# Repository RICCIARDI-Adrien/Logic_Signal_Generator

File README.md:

# Logic Signal Generator

A versatile multi-protocol 1.8V/3.3V/5V logic signal generator powered by a PIC18F25K50.

## Features

* 8 independant channels featuring several standard protocols.
* The microcontroller hardware I2C, UART, SPI and PWM modules are used to provide the signal timings.
* Entirely USB-powered, no need for an external power supply.
* Dedicated power supplies and ground connector to easily power the device under test. The embedded 1.8V and 3.3V power supplies are each able to provide 500mA (these power supplies are derived from the USB power, so the available power could be limited by the USB port).
* On-board switch to quickly select the logic signals output voltage (1.8V, 3.3V or 5V).
* The USB interface is managed by the microcontroller itself and provides a standard USB serial port to the host.
* Simple shell-based text interface through the serial port to interactively configure and define the logic signals to generate.
* The signals are doubled on the output connector to easily connect a logic analyzer.
* PICkit-compatible standard connector to easily program the on-board microcontroller firmware.
* Compact and robust casing designed to bring the signal generator on field.

## Hardware

Bare PCB :

Assembled PCB :

## Casing

The casing is made of 4mm-thick 304 stainless steel.

Bare plates :

Assembled bottom plate, with PCB and hex spacers :

Fully assembled device :  
Top view :

IO and power connectors :

USB connector and IO voltage selection switch :

Power and activity LEDs along with microcontroller programming connector :

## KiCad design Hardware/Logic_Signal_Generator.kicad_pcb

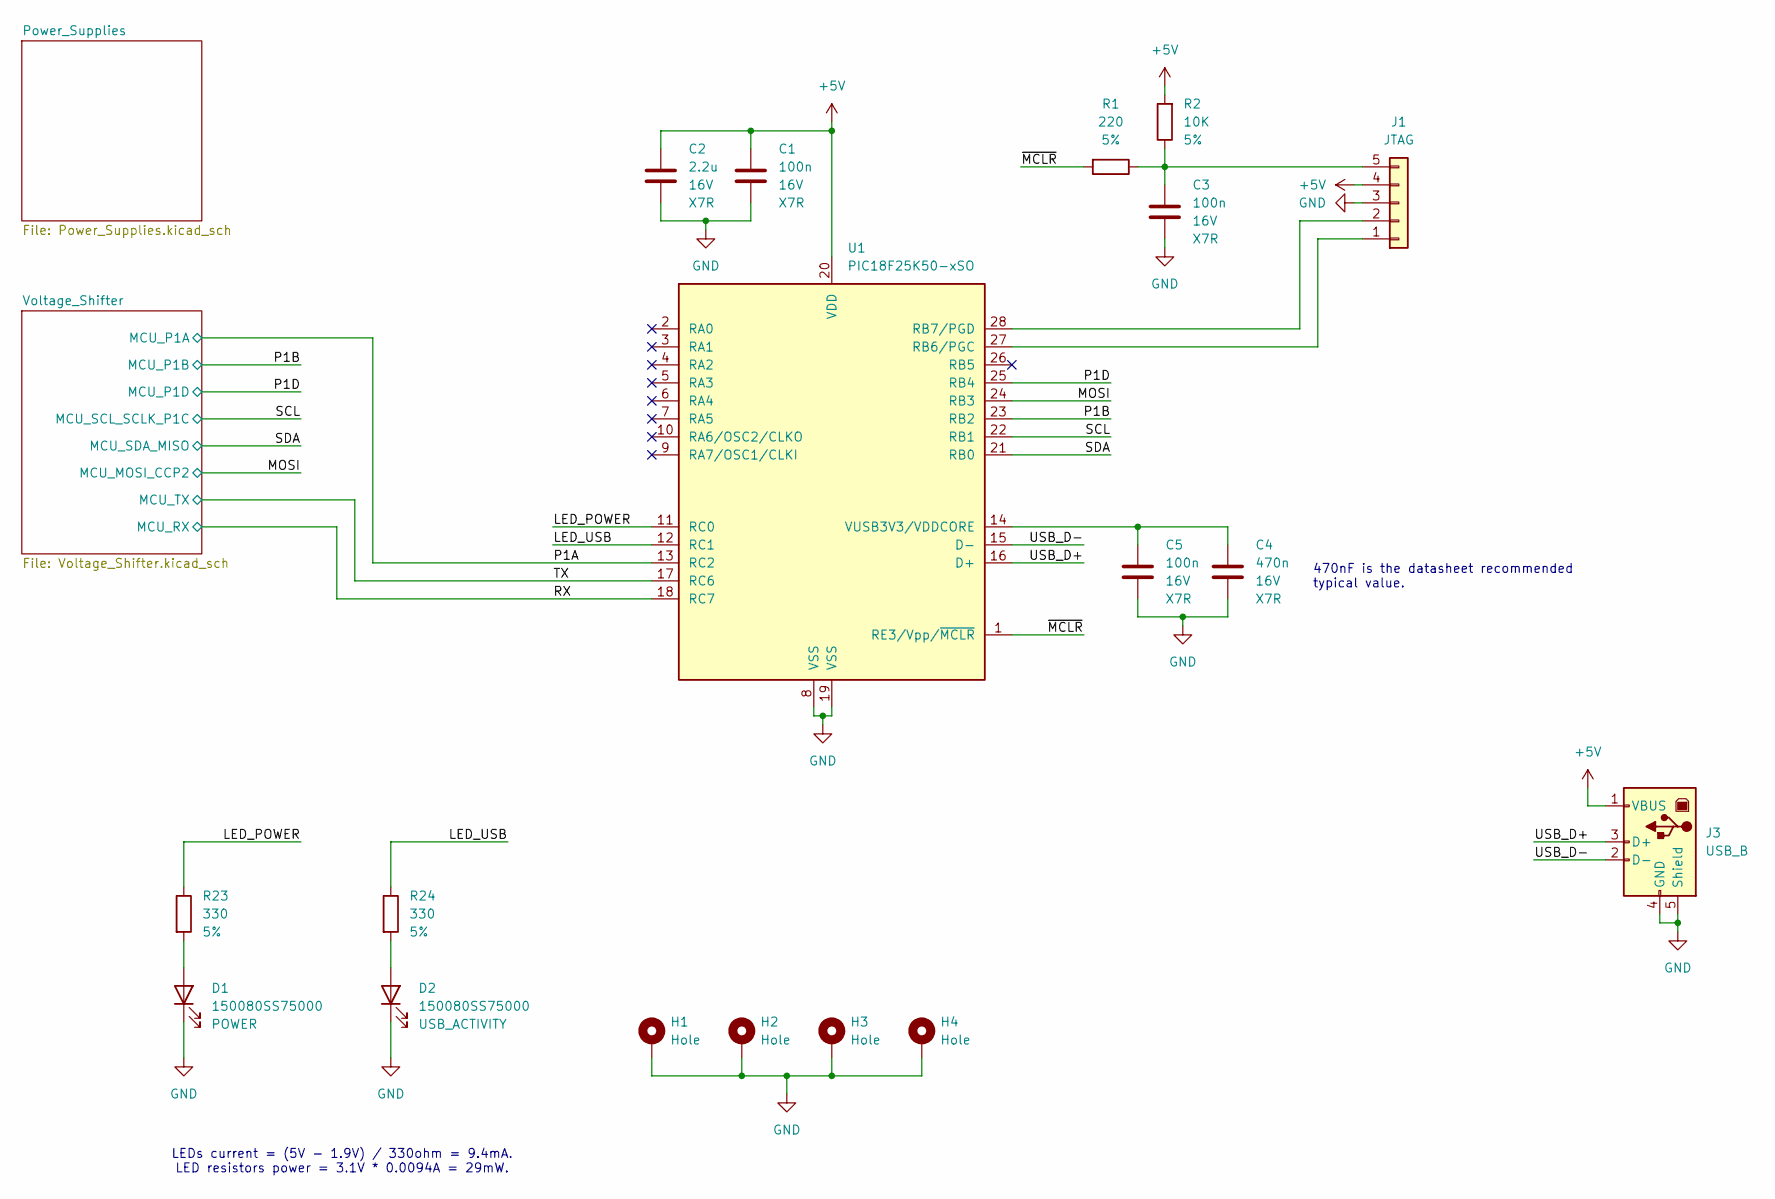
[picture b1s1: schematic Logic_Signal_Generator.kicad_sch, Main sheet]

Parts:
C1, C3, C5: 100n; C_0603_1608Metric_Pad1.08x0.95mm_HandSolder
C2: 2.2u; C_0805_2012Metric_Pad1.18x1.45mm_HandSolder
C4: 470n; C_0603_1608Metric_Pad1.08x0.95mm_HandSolder
D1, D2: 150080SS75000; LED_0805_2012Metric_Pad1.15x1.40mm_HandSolder
H1, H2, H3, H4: Hole; MountingHole_4.5mm_Pad_Via
J1: JTAG; PinHeader_1x05_P2.54mm_Horizontal
J3: USB_B; USB_B_Lumberg_2411_02_Horizontal
R1: 220; R_0603_1608Metric_Pad0.98x0.95mm_HandSolder
R2: 10K; R_0603_1608Metric_Pad0.98x0.95mm_HandSolder
R23, R24: 330; R_1206_3216Metric_Pad1.30x1.75mm_HandSolder
U1: PIC18F25K50-xSO; SOIC-28W_7.5x17.9mm_P1.27mm

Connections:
+5V: C1.1, C2.1, J1.4, J3.1 (VBUS), R2.2, U1.20 (VDD); also elsewhere on the board
/LED_POWER: R23.1, U1.11 (RC0)
/LED_USB: R24.1, U1.12 (RC1)
/MOSI: U1.24 (RB3); also elsewhere on the board
/P1A: U1.13 (RC2); also elsewhere on the board
/P1B: U1.23 (RB2); also elsewhere on the board
/P1D: U1.25 (RB4); also elsewhere on the board
/RX: U1.18 (RC7); also elsewhere on the board
/SCL: U1.22 (RB1); also elsewhere on the board
/SDA: U1.21 (RB0); also elsewhere on the board
/TX: U1.17 (RC6); also elsewhere on the board
/USB_D+: J3.3 (D+), U1.16 (D+)
/USB_D-: J3.2 (D-), U1.15 (D-)
/~MCLR: R1.2, U1.1 (RE3/Vpp/~MCLR)
GND: C1.2, C2.2, C3.2, C4.2, C5.2, D1.1 (K), D2.1 (K), H1.1, H2.1, H3.1, H4.1, J1.3, J3.4 (GND), J3.5 (Shield), U1.8 (VSS), U1.19 (VSS); also elsewhere on the board
unnamed: D1.2 (A), R23.2
unnamed: D2.2 (A), R24.2
unnamed: J1.1, U1.27 (RB6/PGC)
unnamed: J1.2, U1.28 (RB7/PGD)
unnamed: C3.1, J1.5, R1.1, R2.1
unnamed: C4.1, C5.1, U1.14 (VUSB3V3/VDDCORE)

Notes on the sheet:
LEDs current = (5V - 1.9V) / 330ohm = 9.4mA. LED resistors power = 3.1V * 0.0094A = 29mW.
470nF is the datasheet recommended typical value.

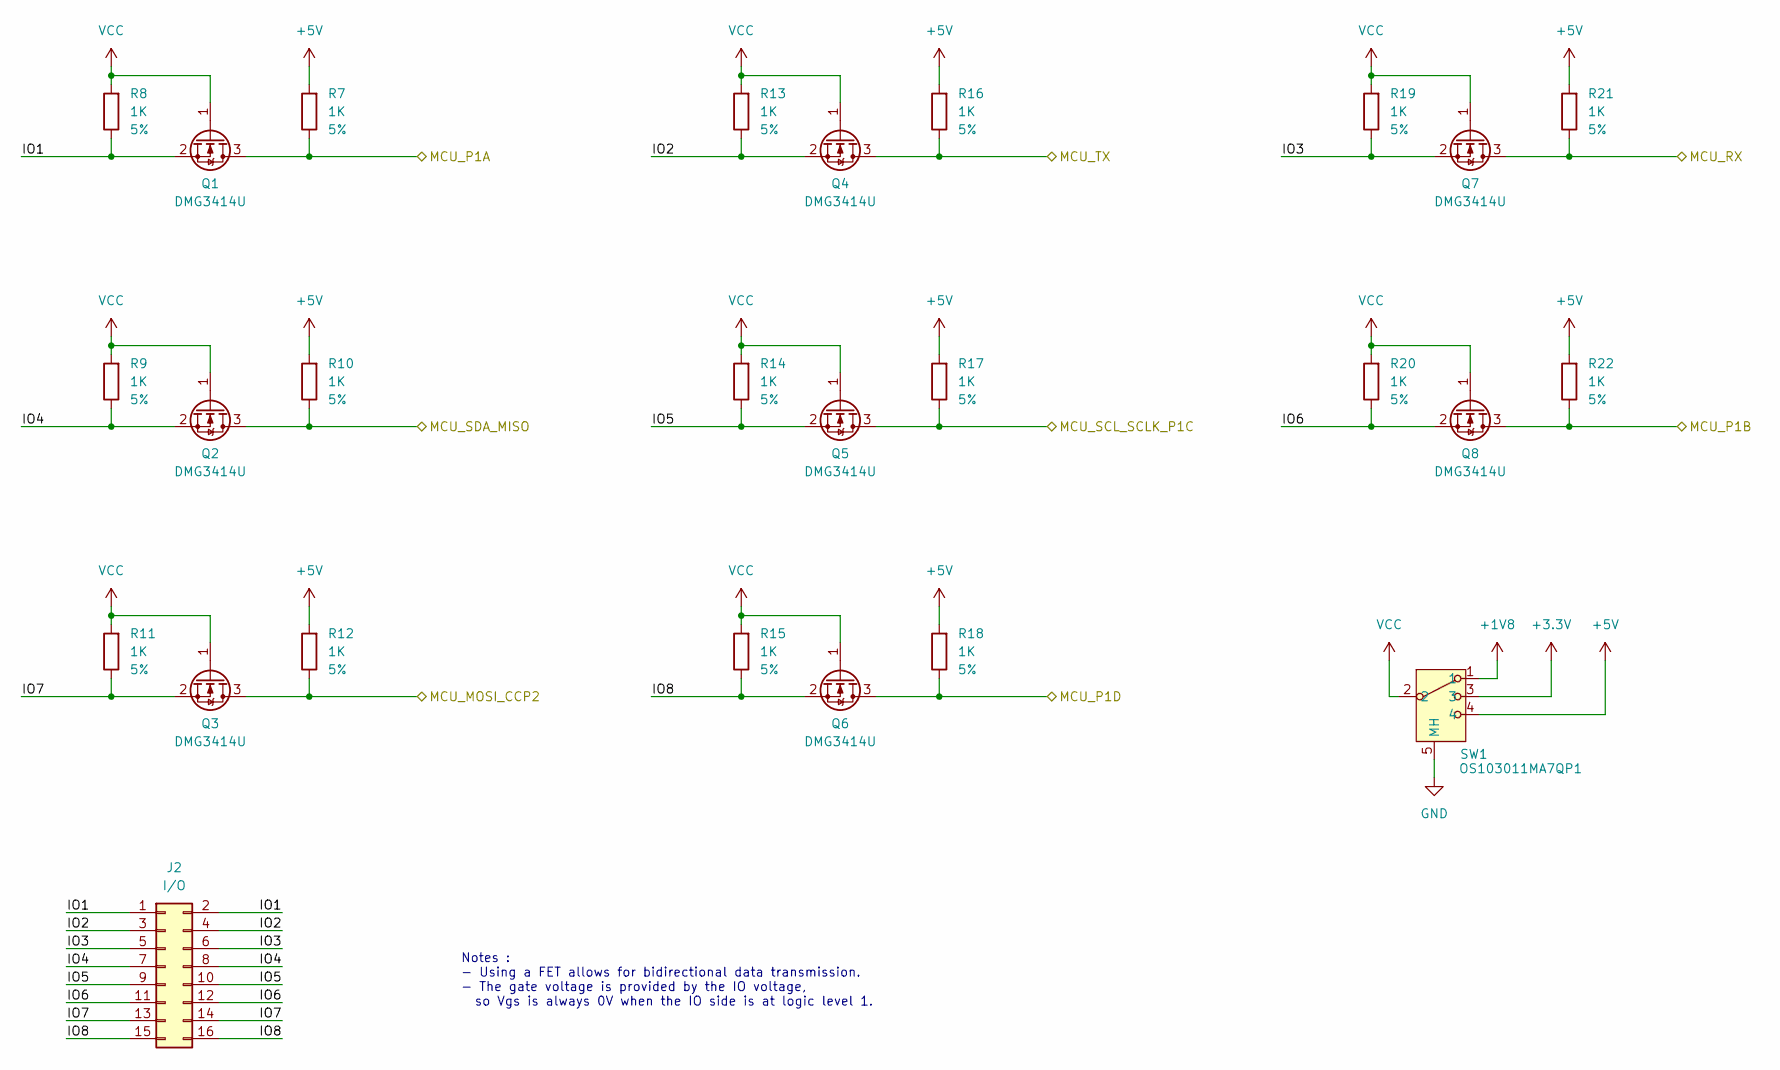
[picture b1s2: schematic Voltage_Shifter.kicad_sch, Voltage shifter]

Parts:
J2: I/O; PinHeader_2x08_P2.54mm_Horizontal
Q1, Q2, Q3, Q4, Q5, Q6, Q7, Q8: DMG3414U; SOT-23
R7, R8, R9, R10, R11, R12, R13, R14, R15, R16, R17, R18, R19, R20, R21, R22: 1K; R_0603_1608Metric_Pad0.98x0.95mm_HandSolder
SW1: OS103011MA7QP1

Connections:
+1V8: SW1.1; also elsewhere on the board
+3.3V: SW1.3; also elsewhere on the board
+5V: R7.2, R10.2, R12.2, R16.2, R17.2, R18.2, R21.2, R22.2, SW1.4; also elsewhere on the board
/MOSI: Q3.3 (D), R12.1; also elsewhere on the board
/P1A: Q1.3 (D), R7.1; also elsewhere on the board
/P1B: Q8.3 (D), R22.1; also elsewhere on the board
/P1D: Q6.3 (D), R18.1; also elsewhere on the board
/RX: Q7.3 (D), R21.1; also elsewhere on the board
/SCL: Q5.3 (D), R17.1; also elsewhere on the board
/SDA: Q2.3 (D), R10.1; also elsewhere on the board
/TX: Q4.3 (D), R16.1; also elsewhere on the board
/Voltage_Shifter/IO1: J2.1, J2.2, Q1.2 (S), R8.1
/Voltage_Shifter/IO2: J2.3, J2.4, Q4.2 (S), R13.1
/Voltage_Shifter/IO3: J2.5, J2.6, Q7.2 (S), R19.1
/Voltage_Shifter/IO4: J2.7, J2.8, Q2.2 (S), R9.1
/Voltage_Shifter/IO5: J2.9, J2.10, Q5.2 (S), R14.1
/Voltage_Shifter/IO6: J2.11, J2.12, Q8.2 (S), R20.1
/Voltage_Shifter/IO7: J2.13, J2.14, Q3.2 (S), R11.1
/Voltage_Shifter/IO8: J2.15, J2.16, Q6.2 (S), R15.1
GND: SW1.5 (MH), SW1.6 (MH); also elsewhere on the board
VCC: Q1.1 (G), Q2.1 (G), Q3.1 (G), Q4.1 (G), Q5.1 (G), Q6.1 (G), Q7.1 (G), Q8.1 (G), R8.2, R9.2, R11.2, R13.2, R14.2, R15.2, R19.2, R20.2, SW1.2

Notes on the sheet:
Notes : - Using a FET allows for bidirectional data transmission. - The gate voltage is provided by the IO voltage, so Vgs is always 0V when the IO side is at logic level 1.

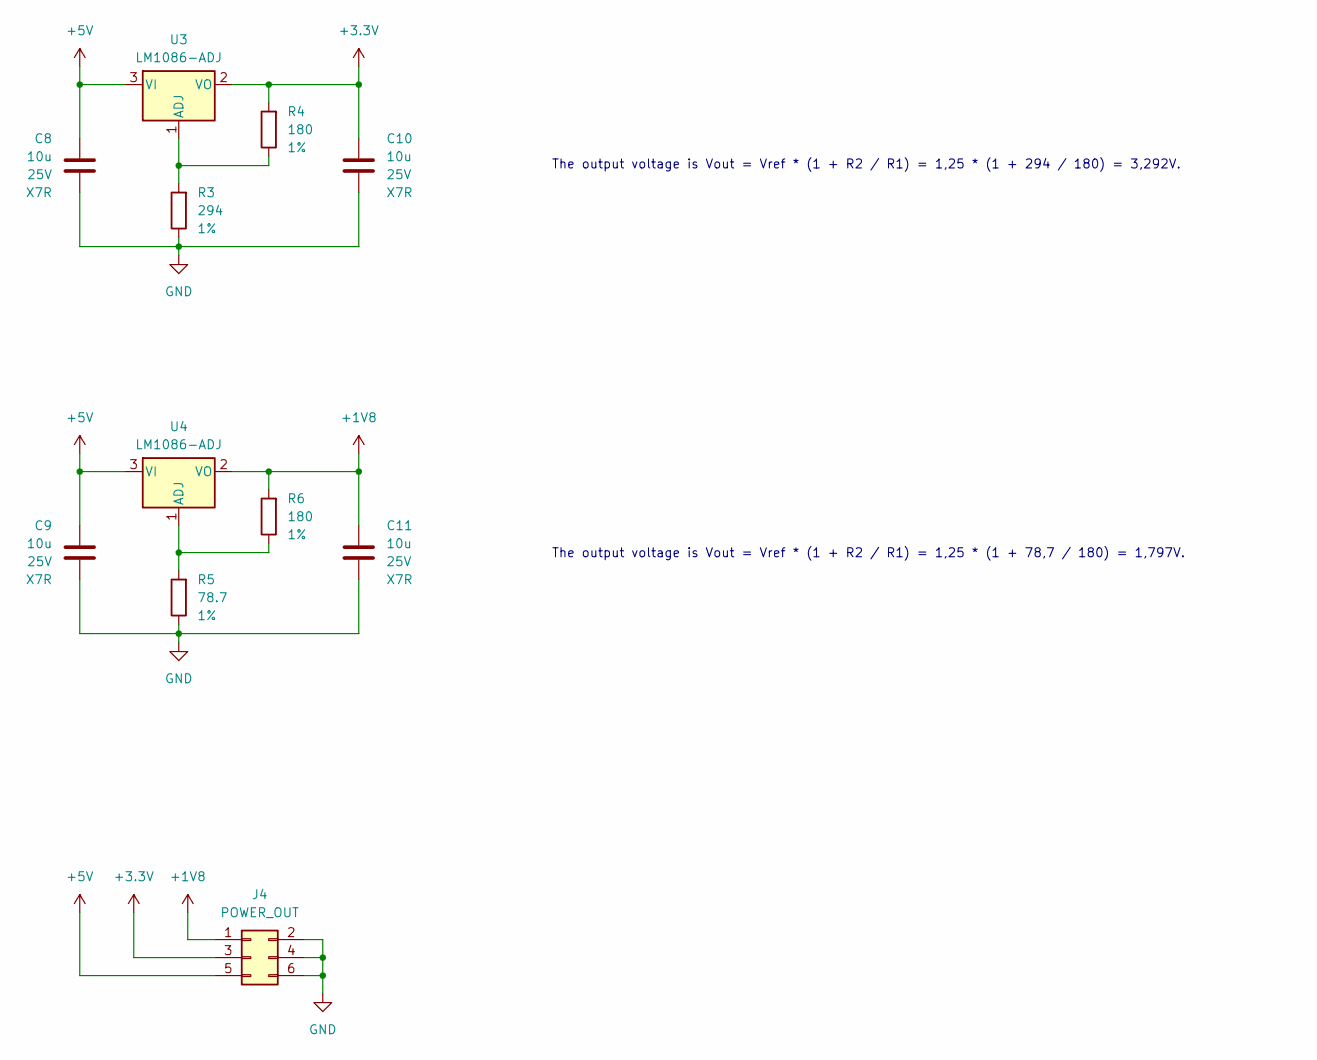
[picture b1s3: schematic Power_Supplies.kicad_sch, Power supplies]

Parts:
C8, C9, C10, C11: 10u; C_0805_2012Metric_Pad1.18x1.45mm_HandSolder
J4: POWER_OUT; PinHeader_2x03_P2.54mm_Horizontal
R3: 294; R_0603_1608Metric_Pad0.98x0.95mm_HandSolder
R4, R6: 180; R_0603_1608Metric_Pad0.98x0.95mm_HandSolder
R5: 78.7; R_0603_1608Metric_Pad0.98x0.95mm_HandSolder
U3, U4: LM1086-ADJ; TO-263-3_TabPin2

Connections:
+1V8: C11.1, J4.1, R6.2, U4.2 (VO); also elsewhere on the board
+3.3V: C10.1, J4.3, R4.2, U3.2 (VO); also elsewhere on the board
+5V: C8.1, C9.1, J4.5, U3.3 (VI), U4.3 (VI); also elsewhere on the board
GND: C8.2, C9.2, C10.2, C11.2, J4.2, J4.4, J4.6, R3.1, R5.1; also elsewhere on the board
unnamed: R3.2, R4.1, U3.1 (ADJ)
unnamed: R5.2, R6.1, U4.1 (ADJ)

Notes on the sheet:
The output voltage is Vout = Vref * (1 + R2 / R1) = 1,25 * (1 + 294 / 180) = 3,292V.
The output voltage is Vout = Vref * (1 + R2 / R1) = 1,25 * (1 + 78,7 / 180) = 1,797V.

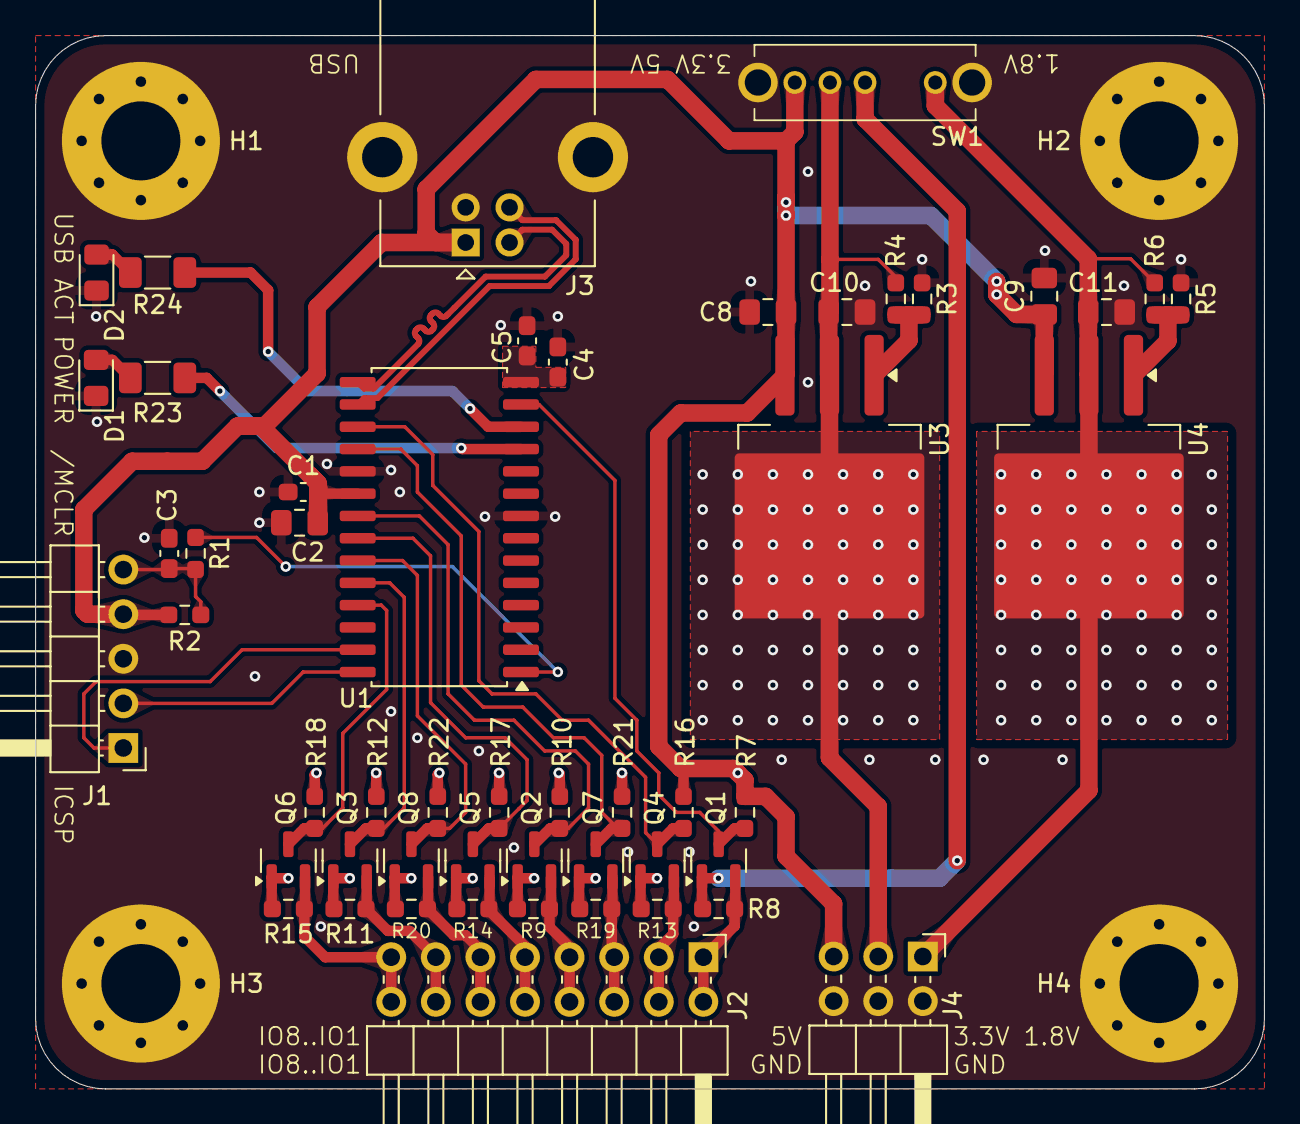
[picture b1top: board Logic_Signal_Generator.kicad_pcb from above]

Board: 2 copper layers, 70.0 x 60.0 mm, 55 parts (0 on the bottom side), 34 nets.

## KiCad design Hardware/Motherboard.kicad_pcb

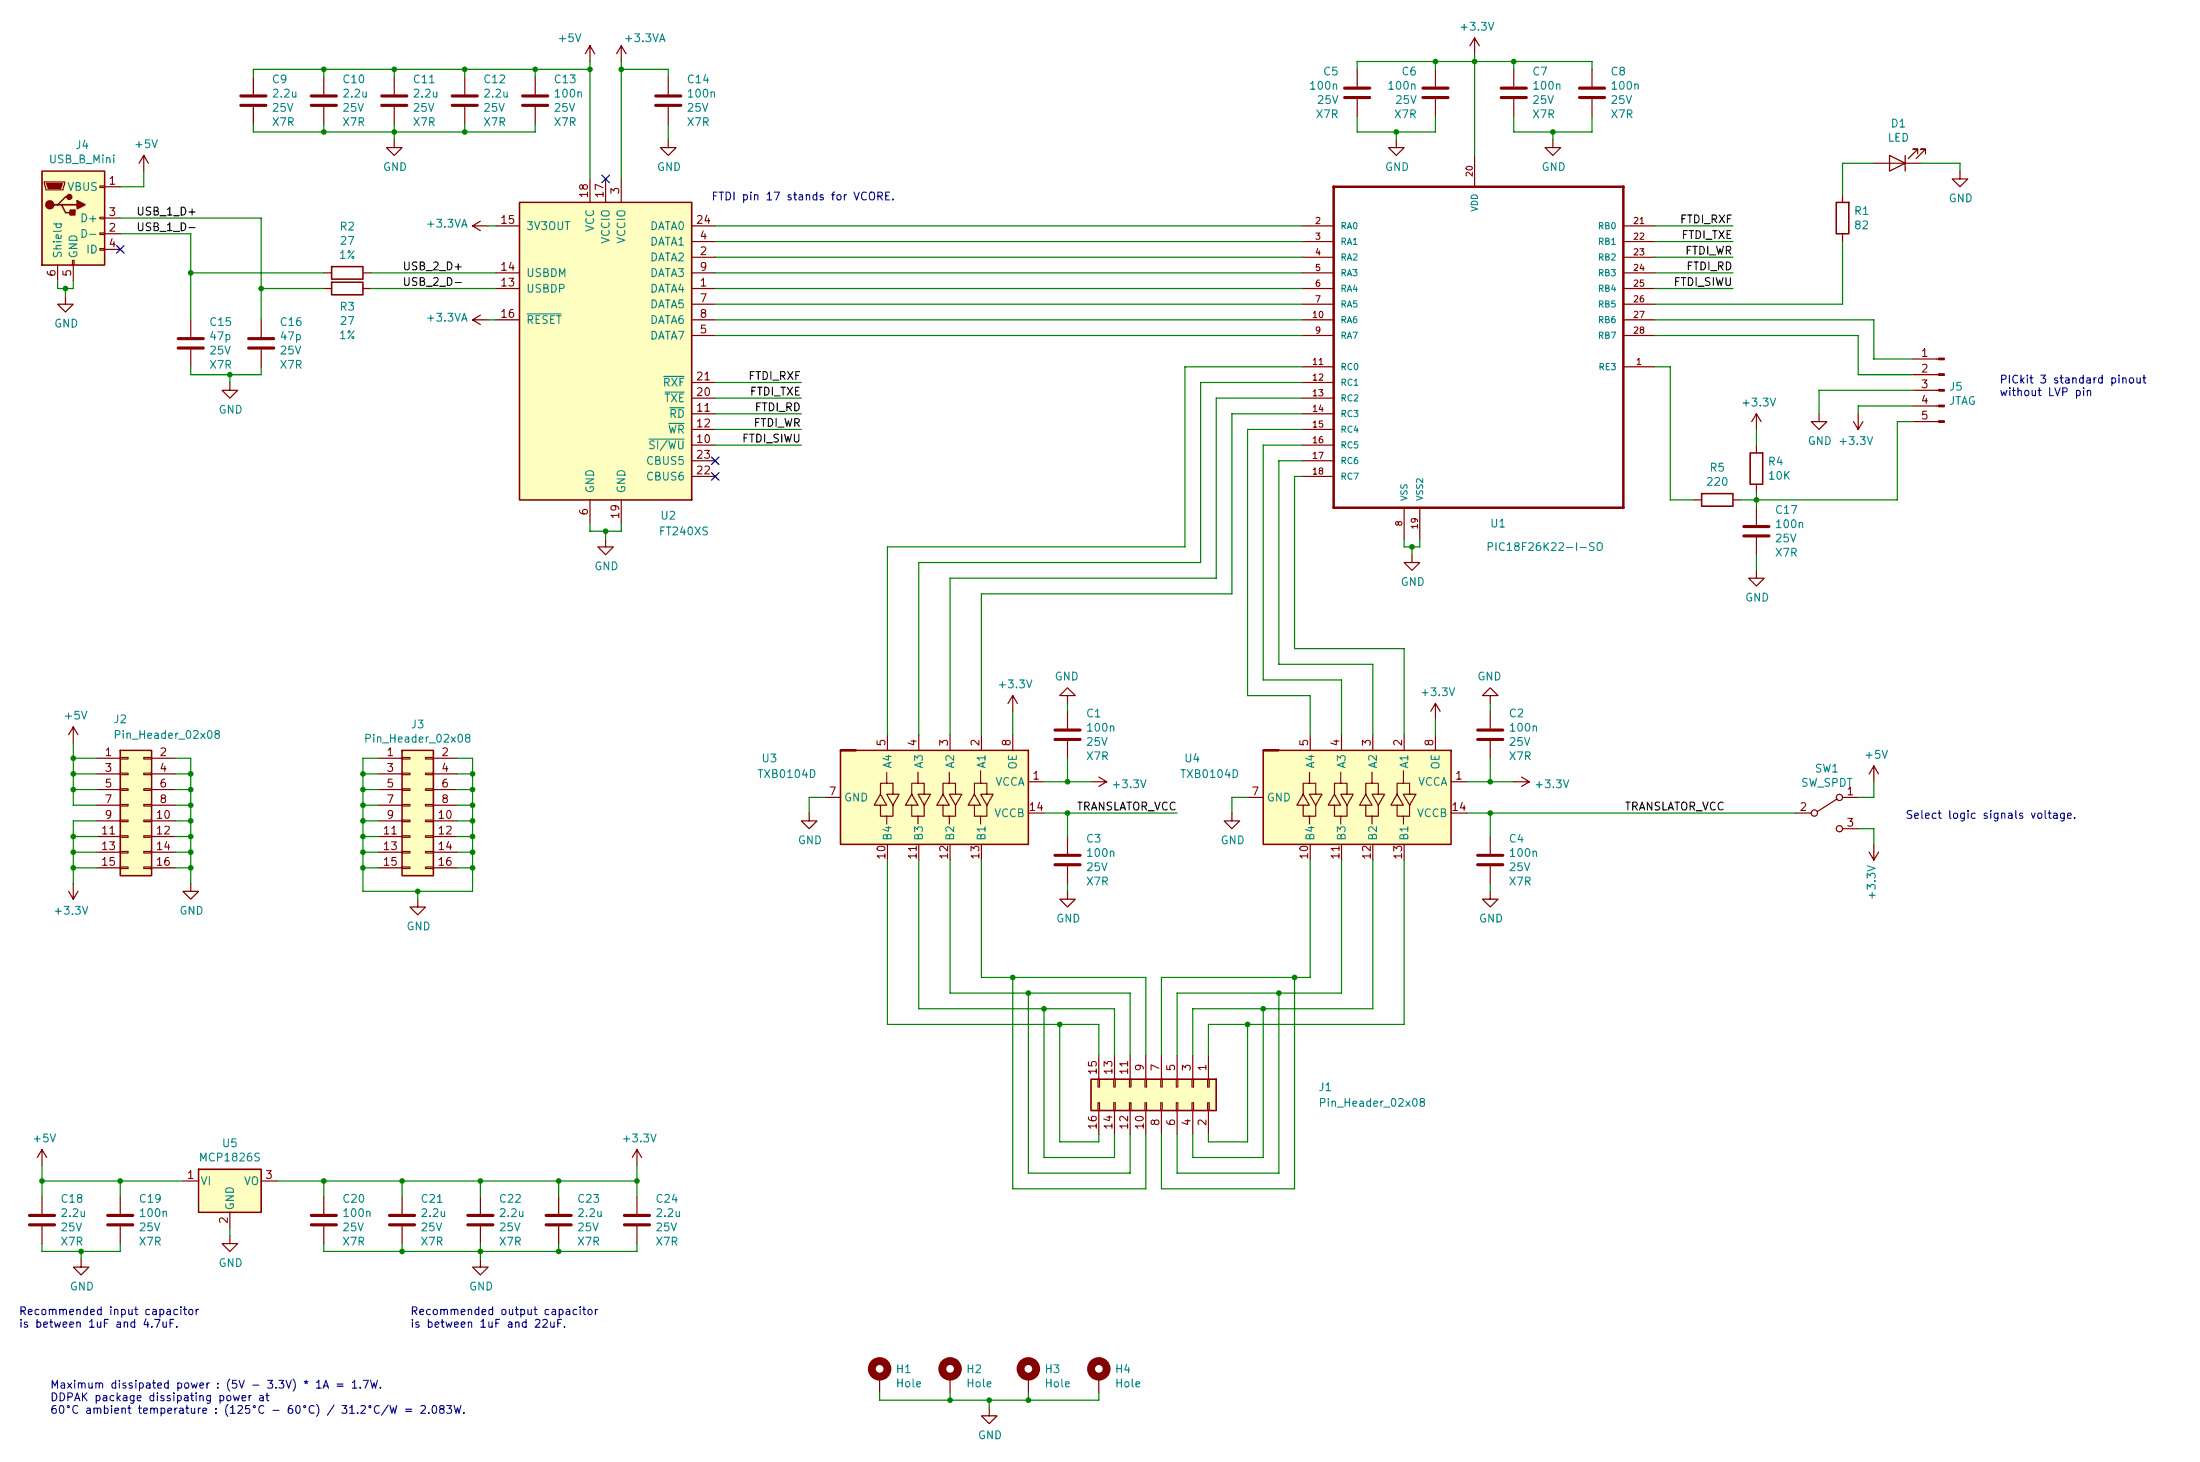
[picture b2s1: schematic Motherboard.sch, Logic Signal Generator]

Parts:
C1, C2, C3, C4, C5, C6, C7, C8, C13, C14, C17, C19, C20: 100n; C_0805_2012Metric_Pad1.15x1.40mm_HandSolder
C9, C10, C11, C12, C18, C21, C22, C23, C24: 2.2u; C_0805_2012Metric_Pad1.15x1.40mm_HandSolder
C15, C16: 47p; C_0805_2012Metric_Pad1.15x1.40mm_HandSolder
D1: LED; LED_D5.0mm
H1, H2, H3, H4: Hole; MountingHole_3mm_Pad
J1, J2, J3: Pin_Header_02x08; PinHeader_2x08_P2.54mm_Horizontal
J4: USB_B_Mini; USB_Mini-B_Lumberg_2486_01_Horizontal
J5: JTAG; PinHeader_1x05_P2.54mm_Horizontal
R1: 82; R_1206_3216Metric_Pad1.42x1.75mm_HandSolder
R2, R3: 27; R_0805_2012Metric_Pad1.15x1.40mm_HandSolder
R4: 10K; R_1206_3216Metric_Pad1.42x1.75mm_HandSolder
R5: 220; R_1206_3216Metric_Pad1.42x1.75mm_HandSolder
SW1: SW_SPDT; SW_CuK_OS102011MA1QN1_SPDT_Angled
U1: PIC18F26K22-I-SO; SOIC-28W_7.5x17.9mm_P1.27mm
U2: FT240XS; SSOP-24_3.9x8.7mm_P0.635mm
U3, U4: TXB0104D; SOIC-14_3.9x8.7mm_P1.27mm
U5: MCP1826S; TO-263-3_TabPin2

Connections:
+3.3VA: C14.1, U2.3 (VCCIO), U2.15 (3V3OUT), U2.16 (~RESET)
+3V3: C1.2, C2.2, C5.1, C6.1, C7.1, C8.1, C20.1, C21.1, C22.1, C23.1, C24.1, J2.9, J2.11, J2.13, J2.15, J5.4, R4.2, SW1.3 (C), U1.20 (VDD), U3.1 (VCCA), U3.8 (OE), U4.1 (VCCA), U4.8 (OE), U5.3 (VO)
+5V: C9.1, C10.1, C11.1, C12.1, C13.1, C18.1, C19.1, J2.1, J2.3, J2.5, J2.7, J4.1 (VBUS), SW1.1 (A), U2.18 (VCC), U5.1 (VI)
/FTDI_RD: U1.24 (RB3), U2.11 (~RD)
/FTDI_RXF: U1.21 (RB0), U2.21 (~RXF)
/FTDI_SIWU: U1.25 (RB4), U2.10 (~SI/WU)
/FTDI_TXE: U1.22 (RB1), U2.20 (~TXE)
/FTDI_WR: U1.23 (RB2), U2.12 (~WR)
/TRANSLATOR_VCC: C3.1, C4.1, SW1.2 (B), U3.14 (VCCB), U4.14 (VCCB)
/USB_1_D+: C16.1, J4.3 (D+), R3.2
/USB_1_D-: C15.1, J4.2 (D-), R2.2
/USB_2_D+: R2.1, U2.14 (USBDM)
/USB_2_D-: R3.1, U2.13 (USBDP)
GND: C1.1, C2.1, C3.2, C4.2, C5.2, C6.2, C7.2, C8.2, C9.2, C10.2, C11.2, C12.2, C13.2, C14.2, C15.2, C16.2, C17.2, C18.2, C19.2, C20.2, C21.2, C22.2, C23.2, C24.2, D1.1 (K), H1.1, H2.1, H3.1, H4.1, J2.2, J2.4, J2.6, J2.8, J2.10, J2.12, J2.14, J2.16, J3.1, J3.2, J3.3, J3.4, J3.5, J3.6, J3.7, J3.8, J3.9, J3.10, J3.11, J3.12, J3.13, J3.14, J3.15, J3.16, J4.5 (GND), J4.6 (Shield), J5.3, U1.8 (VSS), U1.19 (VSS2), U2.6 (GND), U2.19 (GND), U3.7 (GND), U4.7 (GND), U5.2 (GND)
unnamed: C17.1, J5.5, R4.1, R5.1
unnamed: D1.2 (A), R1.2
unnamed: J1.1, J1.2, U4.13 (B1)
unnamed: J1.3, J1.4, U4.12 (B2)
unnamed: J1.5, J1.6, U4.11 (B3)
unnamed: J1.7, J1.8, U4.10 (B4)
unnamed: J1.9, J1.10, U3.13 (B1)
unnamed: J1.11, J1.12, U3.12 (B2)
unnamed: J1.13, J1.14, U3.11 (B3)
unnamed: J1.15, J1.16, U3.10 (B4)
unnamed: J5.1, U1.27 (RB6)
unnamed: J5.2, U1.28 (RB7)
unnamed: R1.1, U1.26 (RB5)
unnamed: R5.2, U1.1 (RE3)
unnamed: U1.2 (RA0), U2.24 (DATA0)
unnamed: U1.3 (RA1), U2.4 (DATA1)
unnamed: U1.4 (RA2), U2.2 (DATA2)
unnamed: U1.5 (RA3), U2.9 (DATA3)
unnamed: U1.6 (RA4), U2.1 (DATA4)
unnamed: U1.7 (RA5), U2.7 (DATA5)
unnamed: U1.9 (RA7), U2.5 (DATA7)
unnamed: U1.10 (RA6), U2.8 (DATA6)
unnamed: U1.11 (RC0), U3.5 (A4)
unnamed: U1.12 (RC1), U3.4 (A3)
unnamed: U1.13 (RC2), U3.3 (A2)
unnamed: U1.14 (RC3), U3.2 (A1)
unnamed: U1.15 (RC4), U4.5 (A4)
unnamed: U1.16 (RC5), U4.4 (A3)
unnamed: U1.17 (RC6), U4.3 (A2)
unnamed: U1.18 (RC7), U4.2 (A1)

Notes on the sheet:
PICkit 3 standard pinout without LVP pin
Maximum dissipated power : (5V - 3.3V) * 1A = 1.7W. DDPAK package dissipating power at 60°C ambient temperature : (125°C - 60°C) / 31.2°C/W = 2.083W.
Recommended input capacitor is between 1uF and 4.7uF.
Recommended output capacitor is between 1uF and 22uF.
FTDI pin 17 stands for VCORE.
Select logic signals voltage.

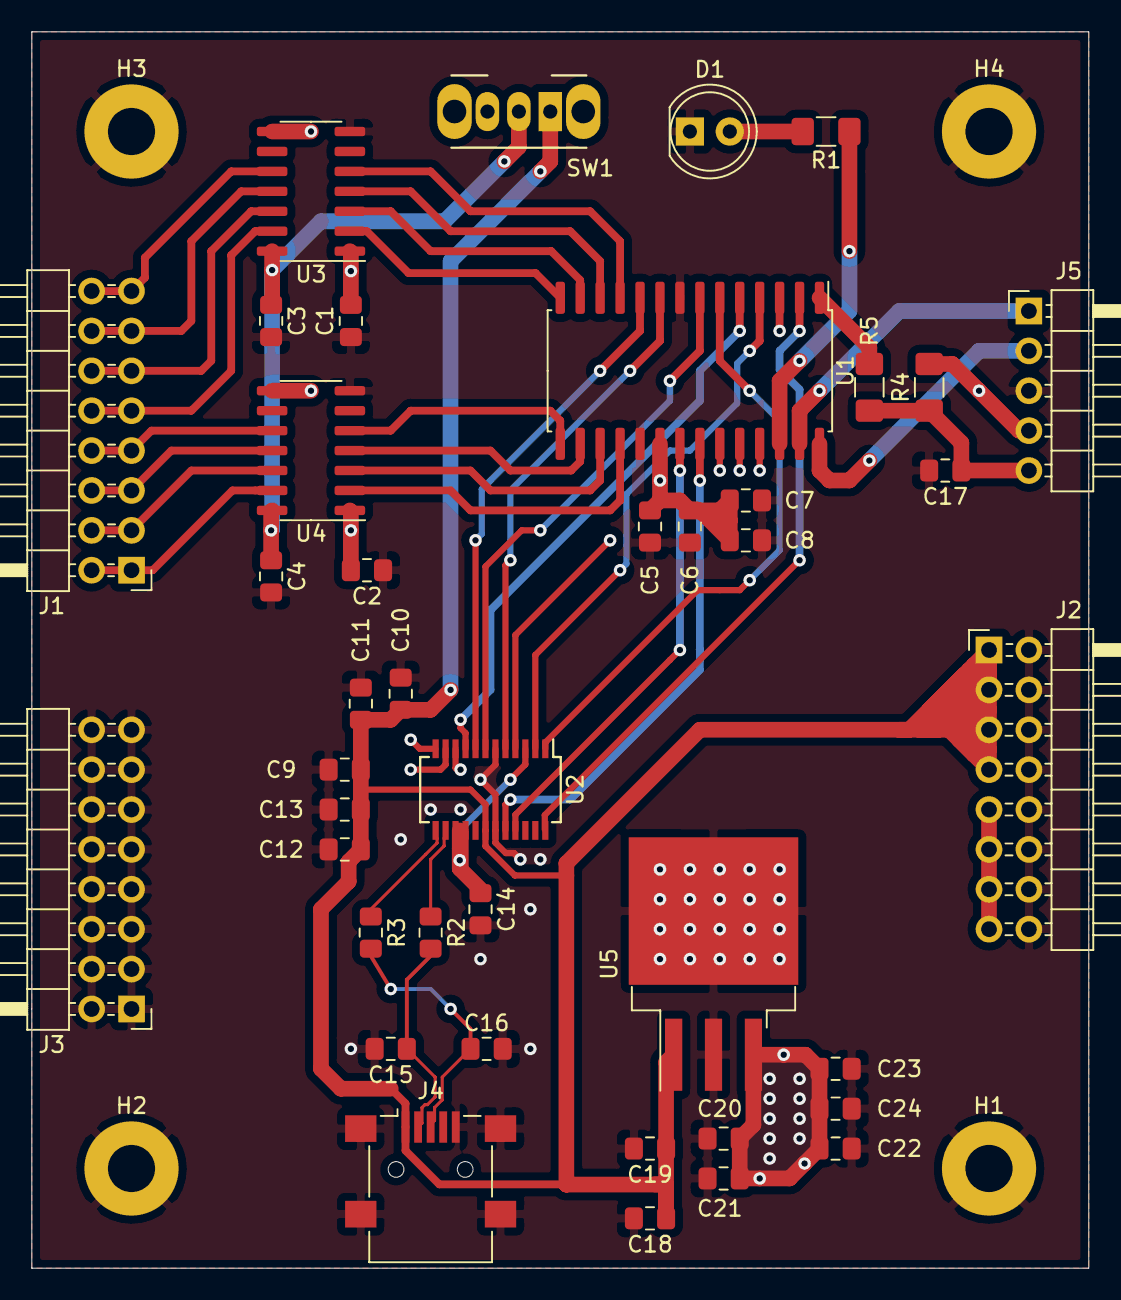
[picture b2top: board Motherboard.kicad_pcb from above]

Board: 4 copper layers, 67.3 x 78.7 mm, 45 parts (0 on the bottom side), 44 nets.

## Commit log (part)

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2020-04-02 Initial commit. Added .gitignore file.
2020-04-02 [Hardware] Started schematic. Microcontroller, voltage translators and pin headers are present.
2020-04-02 [Hardware] Added LDO and led to schematic.
2020-04-02 [Hardware] Added FTDI FIFO and logic signals output voltage switch to schematic.
2020-04-02 [Hardware] Added PCB mounting holes.
2020-04-02 Added README.md.
2020-04-15 [Hardware] Started PCB routing. Switched to 4 layers to have power supply planes.
2020-04-15 [Hardware] Improved some component names placement on PCB.
2025-04-12 [Software] Created the project empty layout.
2025-04-12 [Software] Added the microcontroller fuses configuration.
2025-04-12 [Software] Configured the system clock and added a blinking LED test.
2025-04-17 [Software] Added the logging module that outputs log messages to the UART.
2025-04-22 [Software] Started exploring and implementing the USB support. The only thing the USB device is currently capable of is to attach to the USB bus.
2025-04-22 [Software] Added the dual-priority interrupts support and the generic handler for the USB peripheral.
    Only the USB 'reset' interrupt is detected for now, and only for test purpose.
2025-04-30 [Software] Enabled the microcontroller clock automatic synchronization with the USB host clock.
2025-04-30 [Software] Added USB 'in' packet support (i.e. transmitting data from the device to the host). The USB stack is now able to transmit the device descriptor to the host.
2025-04-30 [Software] Used bit fields to describe the USB hardware endpoint status register, this makes the code easier to understand.
2025-05-20 [Software] Reorganized the USB interrupt to better manage the IN, OUT and SETUP transfers.
2025-05-20 [Software] Added a basic USB data toggling synchronization support and the beginning of the 'set address' USB enumeration step.
2025-05-20 [Software] Fixed the USB string descriptor indexes in the device descriptor : they start at index 1 instead of 0.
2025-05-20 [Software] Added color to the initial log message, so it can be easily spotted.
2025-07-26 [Software] Added more debugging information displayed at the beginning of the USB interrupt handler.
2025-07-26 [Software] Enabled the generation of a map file during the build.
2025-07-26 [Software] Added the support for the USB Device Qualifier descriptor in the enumeration process.
    Also added the ability to stall an endpoint.
2025-07-26 [Software] Improved the USB interface handling during the configuration descriptors enumeration step.
    It is now possible to manage as much interfaces per configuration as there is room in an endpoint buffer.
2025-07-26 [Software] Removed the USB configuration structure and embedded a pointer to the USB configurations directly into the USB device descriptor.
2025-07-26 [Software] Added support to the USB enumeration step for multiple configuration descriptors.
2025-07-27 [Software] Enabled all compiler warnings.
2025-07-27 [Software] Added logging code section macros that allow to automatically discard the section of code when the logs are disabled.
2025-07-27 [Software] Added support for the USB set configuration enumeration step.
2025-07-27 [Software] Updated the USB core module logs with the log sections.
2025-07-27 [Software] Fixed the 'set configuration' USB enumeration step log message that was not displaying the correct configuration value.
2025-07-31 [Software] Limited the device required current to 500mA, otherwise the host may refuse to select the corresponding USB configuration.
2025-07-31 [Software] Unified the USB device descriptor class and protocol codes.
2025-07-31 [Software] Added the USB interfaces description matching the CDC ACM specifications.
2025-07-31 [Software] Added a way to configure the hardware USB endpoints along with the various descriptors.
2025-07-31 [Software] Replaced the calls to memcpy() in the USB module by a custom macro to fix a weird bug where some unrelated variables were overwritten after the memcpy() call.
2025-07-31 [Software] Added the calling of the appropriate callback when USB data is received by an endpoint.
2025-08-01 [Software] Moved all the handling of non standard USB setup requests to the registered callbacks.
2025-08-01 [Software] Started the implementation of the USB CDC ACM, starting with an empty callback for the ACM control endpoint.
2025-08-01 [Software] Added the USB CDC ACM PSTN Set Line Coding request support.
2025-08-03 [Software] Fixed consecutive USB OUT transfers not triggering the transfer interrupt by clearing the USB interrupt flags in the correct order.
2025-08-03 [Software] Deduplicated the USB USTAT register information retrieval.
2025-08-03 [Software] Added support for the USB handshake ACK packets.
2025-08-03 [Software] Added support for regular USB OUT packets.
2025-08-03 [Software] Fixed the configuration of the USB hardware endpoints other than 0.
2025-08-03 [Software] Added a simple USB CDC echo test.
2025-08-23 [Software] Allowed the USB stack to call a callback when an IN transfer has been terminated and acknowledged.
2025-08-24 [Software] Moved the USB CDC private types from the header to the source file, as they don't need to be public and complexify the API.
2025-08-24 [Software] Added an API function to write an USB CDC ACM data string to the host.
    Also added support for the transmission flow control.
2025-08-24 [Software] Allowed to send USB CDC ACM strings of data exceeding the USB packet size.
2025-08-25 [Software] Added the USB CDC ACM callback that retrieves the received data bytes and stores them into an internal circular buffer.
2025-08-25 [Software] Added USB core macros to enable or disable the USB peripheral interrupts.
2025-08-25 [Software] Added an USB CDC ACM API function to read a received character.
2025-08-25 [Software] Replaced the strlen() call by a custom string size computation in the USBCommunicationsWriteCharacter() function.
    This allows to save some bytes and also to make sure the string computation will behave as expected.
2025-08-25 [Software] Started implementing the shell commands reading.
2025-08-25 [Software] Added a way to detect that the USB CDC ACM communication link is ready.
2025-08-25 [Software] Improved the shell by neutralizing the VT100 escape sequences and adding support for the UNIX Ctrl+C, Ctrl+D and Ctrl+U key combinations.
2025-08-26 [Software] Added the shell commands processing core.
2025-08-26 [Software] Added the shell "help" command.
2025-08-26 [Software] Added a function to more easily compare a shell token with a string.
2025-08-26 [Software] Added the "i2C-configure" shell command.
2025-08-26 [Software] Added the API function to configure the MSSP peripheral as I2C master.
    Also renamed the MSSPI2CSetFrequency() function to automatically gather all I2C and future SPI functions.
2025-08-26 [Software] Added the I2C start, stop, read and write API functions.
2025-08-30 [Software] Added an utility function to convert a hexadecimal number from a string to its binary representation.
2025-08-30 [Software] Started implementing the "i2c" shell command. Made the skeleton of the I2C commands parser.
2025-08-30 [Software] Added a function to convert a decimal number string to its binary representation.
2025-08-30 [Software] Finished implementing the command line parsing part of the "i2c" shell command.
2025-08-30 [Software] Started implementing the I2C commands execution part of the "i2c" shell command. Start and stop commands are working.
2025-08-30 [Software] Moved the ShellConvertNumericalArgumentToBinary() function to the Shell module to make it available to other commands.
2025-08-30 [Software] Fixed two bugs in the ShellConvertNumericalArgumentToBinary() function.
    - The string terminating character swapped with a 0 was not restored in case no digits were provided after the 'h' character.
    - After converting a hexadecimal number, the command line string was messed by one character.
2025-08-30 [Software] Fixed the shell "i2c" command reporting incorrect slave write NACK.
2025-08-31 [Software] Added an USB activity LED, flashing when USB transfers occur.
2025-08-31 [Software] Enabled the level 2 optimizations for the firmware release build.
2025-09-02 [Software] Fixed the "i2c-scan" shell command hanging after a slave sent an ACK.
2025-09-02 [Hardware] Added a new empty project.
2025-09-02 [Hardware] Added the microcontroller and the supporting hardware to the schematic.
2025-09-02 [Hardware] Added the voltage translator and the USB connector to the schematic.
2025-09-09 [Hardware] Replaced the TXS0108E voltage shifter by discrete N-MOSFET transistors.
    The TXS0108E was not working well during prototyping, it had difficulties determining the direction of the data transfer.
    The microcontroller power supply has been switched from +3.3V to +5V to always provide the highest supported voltage on the N-MOSFET drain.
2025-09-11 [Hardware] Added the output voltage selection switch.
2025-09-11 [Hardware] Added a pin header connector to provide the output power supply.
2025-09-13 [Hardware] Added the missing pin number 3 to the OS103011MA7QP1 switch.
2025-09-13 [Hardware] Made an initial placement of the components on the PCB.
2025-09-13 [Hardware] Added the mounting holes and the PCB edges.
2025-09-13 [Hardware] Enabled PCB teardrops.
2025-09-13 [Hardware] Routed the USB full speed traces trying to keep a matched length and a 45ohm odd differential impedance.
2025-09-13 [Hardware] Routed the voltage regulators.
2025-09-13 [Hardware] Routed all but the LEDs.
    Changed the IOs order to help the routing.
2025-09-13 [Hardware] Added the LDO thermal pads and the connectors and LEDs silkscreen marking.
2025-09-13 [Hardware] Fixed all remaining silkscreen-related PCB warnings.
2025-09-13 [Hardware] Added the USB connector 3D model to the PCB.
2025-09-13 [Hardware] Set the grid and drilling coordinates origin onto the PCB.
2025-09-13 [Hardware] Set the PCB STEP file export path.
2025-09-13 [Hardware] Improved the USB connector and the "/MCLR" silkscreen marking on the PCB.
2025-09-13 [Hardware] Added the missing value for the switch into the schematic.
2025-09-13 [Hardware] Also grouped the components per value 2 and 3 fields when exporting the bill of materials.
2025-09-14 [Software] Added a shell function to display a dump of a data buffer content.
2025-09-14 [Software] Upgraded the shell I2C reading command by showing a full dump of the read data.
2025-09-14 [Software] Disabled almost most of the Ctrl+Letter combinations for the shell, as they could mess it.
2025-09-14 [Software] Assigned the final pin to the USB activity LED.
2025-09-14 [Software] Added the SPI support to the MSSP module.
2025-09-22 [Software] Disabled the USB stack debug logs that were enabled by default.
2025-09-22 [Software] Started implementing the shell "spi" command. Added the command arguments parsing.
2025-09-22 [Software] Added the "spi" shell command logic.
2025-09-22 [Software] Fixed the "read" data dump displaying of the "i2c" shell command.
2025-09-24 [Software] Lighted the power LED when firmware has booted.
2025-09-24 [Software] Added the ability to flash the firmware by invoking the "make flash" command.
2025-09-24 Updated the project features list in the README.md.
2025-10-16 [Casing] Started the casing design by importing the PCB and the hex spacer models.
2025-10-16 [Casing] Added the sketch of a full plate.
2025-10-16 [Casing] Created the bottom plate model and positionned the PCB and the hex spacers.
2025-10-16 [Casing] Added the top plate.
2025-10-28 Added casing pictures to the README.md.
2025-10-29 [Software] Added the "version" shell command.
2026-01-04 [Software] Added support for the compiler v3.10 and its now separate Device Family Pack files.
2026-01-08 [Software] Made the USB "get device descriptor" setup request return only the requested amount of bytes.
    This made the USB serial port fully work on macOS.
2026-01-08 [Software] Bumped the firmware version to 1.1.
    The major change is that the USB serial port is now working reliably on Linux, Windows and macOS.
